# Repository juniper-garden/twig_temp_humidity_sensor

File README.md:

# twig_temp_humidity_sensor
Hardware files for the temperature and humidity sensor

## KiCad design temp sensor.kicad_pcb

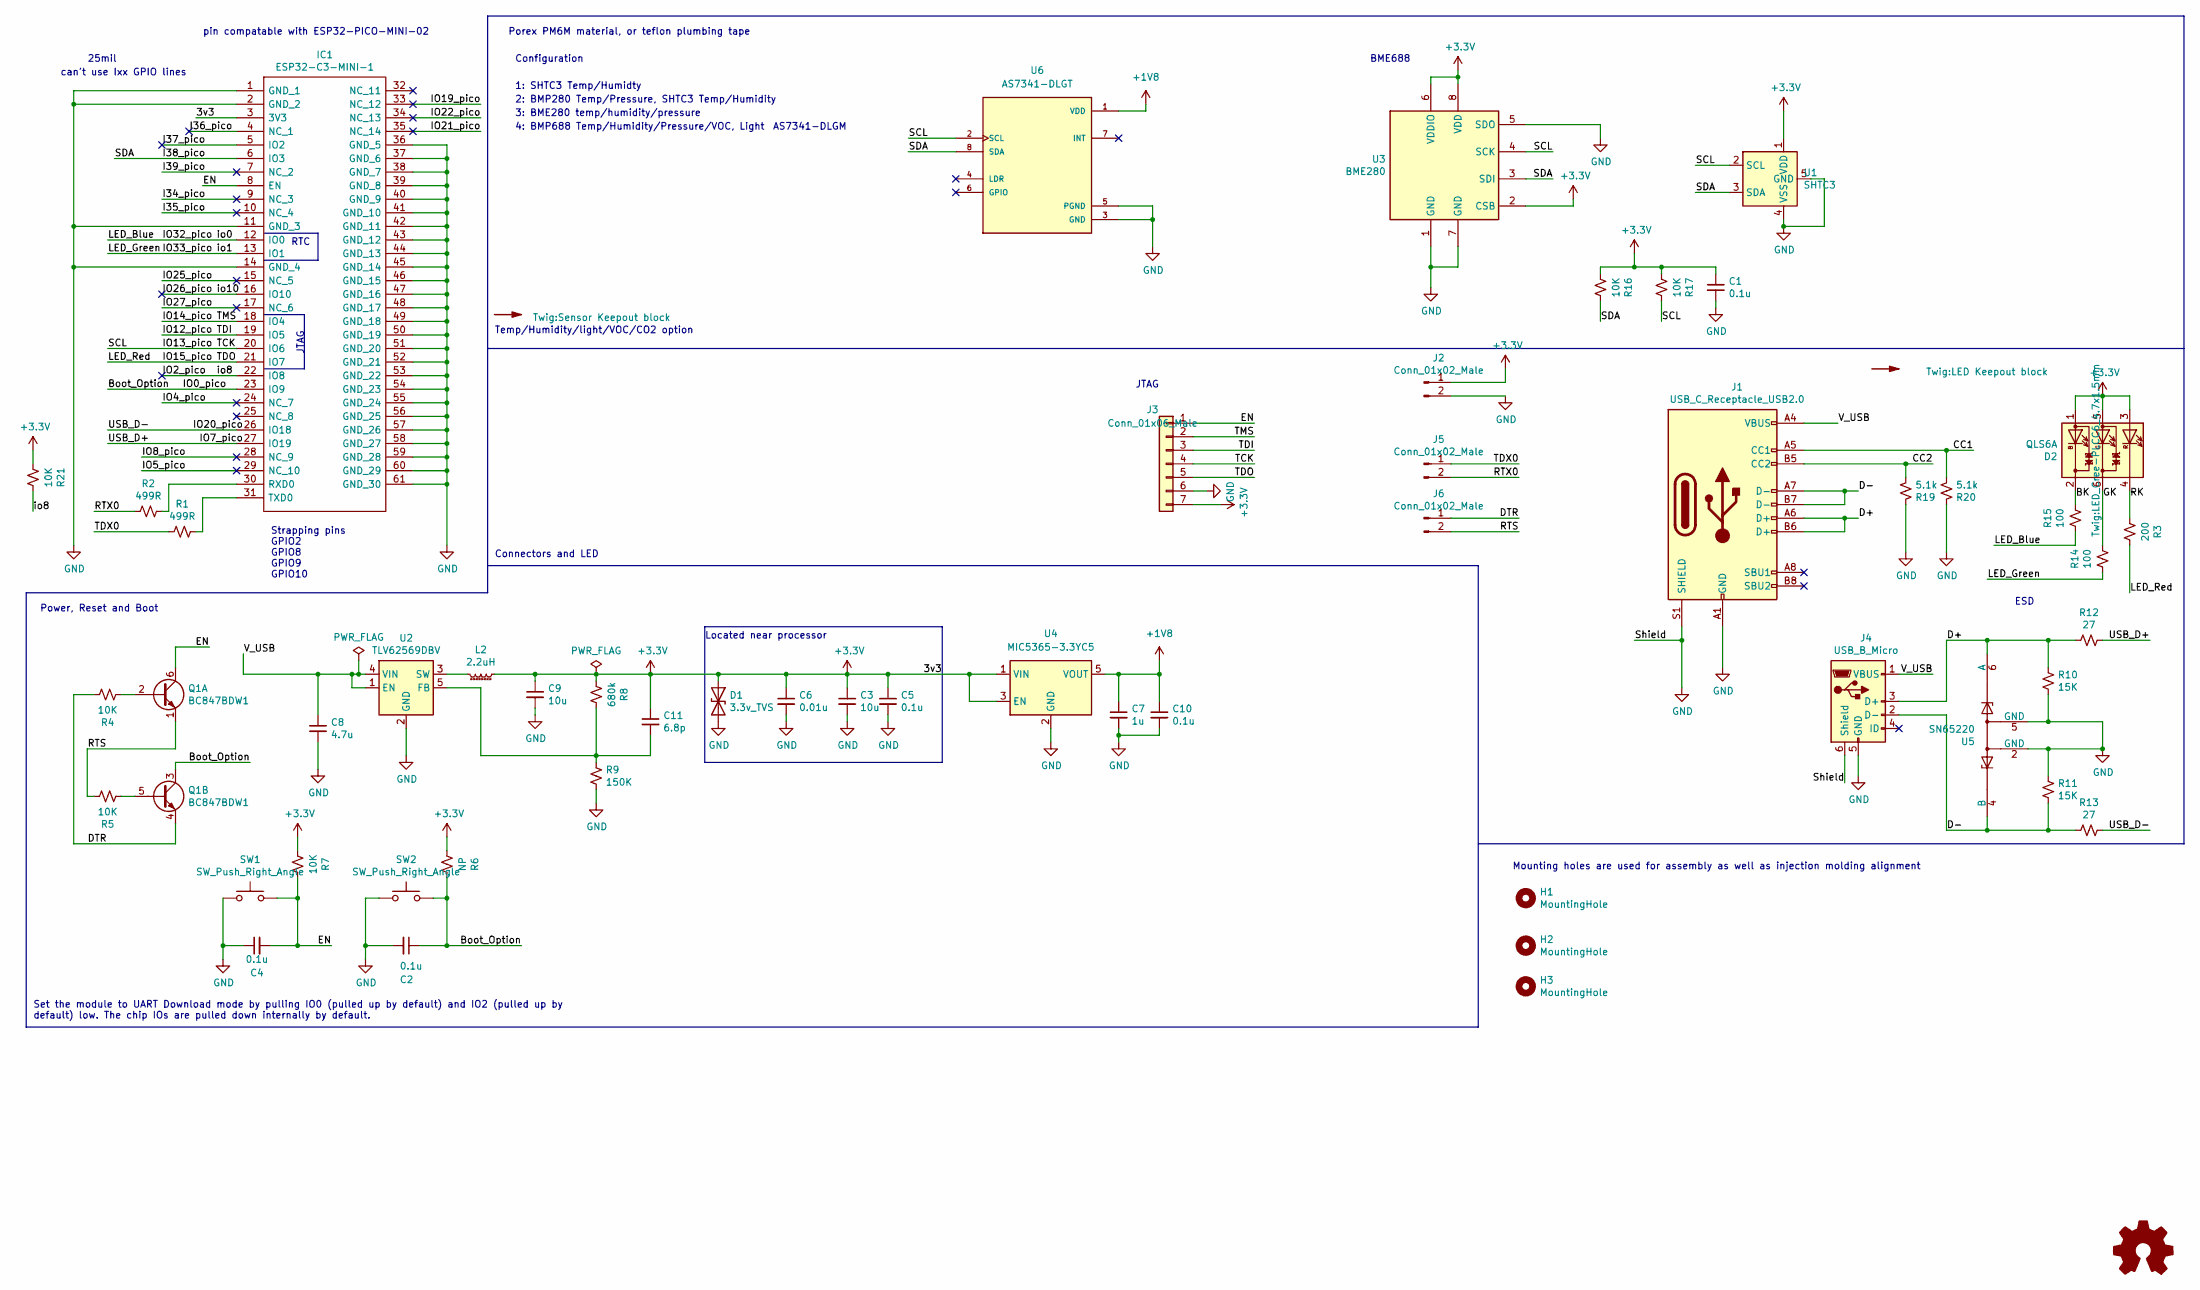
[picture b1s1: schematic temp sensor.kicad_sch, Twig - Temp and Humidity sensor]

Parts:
C1, C2, C4, C5, C10: 0.1u; C_0402_1005Metric; Manufacturer_Part_Number EMK105B7104KVHF; Mouser Part Number 963-EMK105B7104KVHF
C3, C9: 10u; C_1206_3216Metric_Pad1.42x1.75mm_HandSolder; Manufacturer_Part_Number LMK212ABJ106MG-T; Mouser Part Number 963-LMK212ABJ106MG-T
C6: 0.01u; C_0402_1005Metric; Manufacturer_Part_Number EMK105B7103KVHF; Mouser Part Number 963-EMK105B7103KVHF
C7: 1u; C_0603_1608Metric; Manufacturer_Part_Number EMK107B7105KA-T; Mouser Part Number 963-EMK107B7105KA-T
C8: 4.7u; C_0805_2012Metric; Manufacturer_Part_Number JMK107C6475KA-T; Mouser Part Number 963-JMK107C6475KA-T
C11: 6.8p; C_0402_1005Metric; Manufacturer_Part_Number EMK105B7103KVHF; Mouser Part Number 963-EMK105B7103KVHF
D1: 3.3v_TVS; D_SOD-323; Manufacturer_Part_Number SD03C-7; Mouser Part Number 621-SD03C-7
D2: QLS6A; LED_Cree-PLCC6_4.7x1.5mm; Manufacturer_Part_Number QLS6A-FKW-CNSNSF043; Mouser Part Number 941-QLS6AFKWNSNSF043
H1, H2, H3: MountingHole; CorePin_1.15mm; PARTREV V3
IC1: ESP32-C3-MINI-1; ESP32C3MINI1; Manufacturer_Part_Number ESP32-C3-MINI-1-H4; Mouser Part Number 356-ESP32-C3-MINI1H4
J1: USB_C_Receptacle_USB2.0; USB_C_Receptacle_HRO_TYPE-C-31-M-12; Manufacturer_Part_Number USB4105-GF-A; Mouser Part Number 640-USB4105-GF-A
J2, J5, J6: Conn_01x02_Male; PinHeader_1x02_P2.54mm_Vertical_SMD_Pin1Left
J3: Conn_01x06_Male; PinHeader_1x07_P1.00mm_Vertical_SMD_Pin1Right
J4: USB_B_Micro; USB_Micro-B_Molex-105017-0001; Manufacturer_Part_Number 105017-0001; Mouser Part Number 538-105017-0001
L2: 2.2uH; L_Taiyo-Yuden_MD-4040; Manufacturer_Part_Number MDMK4040T2R2MM; Mouser Part Number 963-MDMK4040T2R2MM
LOGO1: Logo_Open_Hardware_Small; FabDrawing-2Layer-Metric
Q1: BC847BDW1; SOT-363_SC-70-6; Manufacturer_Part_Number BC847BDW1T1G; Mouser Part Number 863-BC847BDW1T1G
R1, R2: 499R; R_0402_1005Metric; Manufacturer_Part_Number CR0603-FX-4990ELF; Mouser Part Number 652-CR0603FX-4990ELF
R3: 200; R_0402_1005Metric; Manufacturer_Part_Number CR0603-FX-2000ELF; Mouser Part Number 652-CR0603-FX2000ELF
R4, R5, R7, R16, R17, R21: 10K; R_0402_1005Metric; Manufacturer_Part_Number ESR03EZPJ103; Mouser Part Number 755-ESR03EZPJ103
R6: NP; R_0402_1005Metric; Manufacturer_Part_Number ESR03EZPJ103; Mouser Part Number 755-ESR03EZPJ103
R8: 680k; R_0402_1005Metric; Manufacturer_Part_Number RC0603FR-13680KL; Mouser Part Number 603-RC0603FR-13680KL
R9: 150K; R_0402_1005Metric; Manufacturer_Part_Number RC0603FR-07150KL; Mouser Part Number 603-RC0603FR-07150KL
R10, R11: 15K; R_0402_1005Metric; Manufacturer_Part_Number RC0603FR-1315KL; Mouser Part Number 603-RC0603FR-1315KL
R12, R13: 27; R_0402_1005Metric; Manufacturer_Part_Number RK73B1JTTDD270J; Mouser Part Number 660-RK73B1JTTDD270J
R14, R15: 100; R_0402_1005Metric; Manufacturer_Part_Number RC0603JR-07100RL; Mouser Part Number 603-RC0603JR-07100RL
R19, R20: 5.1k; R_0402_1005Metric; Manufacturer_Part_Number CR0603-FX-5101ELF; Mouser Part Number 652-CR0603FX-5101ELF
SW1, SW2: SW_Push_Right_Angle; SW_Push_1P1T-MP_NO_Horizontal_TL6340; Manufacturer_Part_Number TL6340AF160QG; Mouser Price/Stock $0.48/10000
SYM1: SYM_Arrow_Normal; Sensor Keepout block
SYM2: SYM_Arrow_Normal; LED Keepout block
U1: SHTC3; Sensirion_DFN-4-1EP_2x2mm_P1mm_EP0.7x1.6mm; Manufacturer_Part_Number SHTC3; Mouser Part Number 403-SHTC3
U2: TLV62569DBV; SOT-23-5; Manufacturer_Part_Number TLV62569DBVR; Mouser Part Number 595-TLV62569DBVR
U3: BME280; Bosch_LGA-8_2.5x2.5mm_P0.65mm_ClockwisePinNumbering; Manufacturer_Part_Number BME280; Mouser Part Number 262-BME280
U4: MIC5365-3.3YC5; SOT-353_SC-70-5
U5: SN65220; SOT-23-6; Manufacturer_Part_Number SN65220DBVT; Mouser Part Number 595-SN65220DBVT
U6: AS7341-DLGT; PSON80P310X200X110-8N; PARTREV V3

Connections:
+1V8: C7.1, C10.1, U4.5 (VOUT), U6.1 (VDD)
+3V3: C1.1, C3.1, C5.1, C6.1, C9.1, C11.1, D1.1 (A1), D2.1 (AB), D2.3 (AR), D2.5 (AG), IC1.3 (3V3), J2.1, J3.7, L2.2, R6.2, R7.2, R8.2, R16.2, R17.2, R21.2, U1.1 (VDD), U3.2 (CSB), U3.6 (VDDIO), U3.8 (VDD), U4.1 (VIN), U4.3 (EN)
/BK: D2.2 (KB), R15.1
/Boot_Option: C2.1, IC1.23 (IO9), Q1.3 (C2), R6.1, SW2.2
/CC1: J1.A5 (CC1), R20.2
/CC2: J1.B5 (CC2), R19.2
/D+: J1.A6 (D+), J1.B6 (D+), J4.3 (D+), R10.1, R12.1, U5.1, U5.6 (A)
/D-: J1.A7 (D-), J1.B7 (D-), J4.2 (D-), R11.2, R13.1, U5.3, U5.4 (B)
/DTR: J6.1, Q1.4 (E2), R4.1
/EN: C4.2, IC1.8 (EN), J3.1, Q1.6 (C1), R7.1, SW1.2
/GK: D2.6 (KR), R14.1
/I34_pico: IC1.9 (NC_3)
/I35_pico: IC1.10 (NC_4)
/I36_pico: IC1.4 (NC_1)
/I37_pico: IC1.5 (IO2)
/I38_pico: IC1.6 (IO3), R16.1, U1.3 (SDA), U3.3 (SDI), U6.8 (SDA)
/I39_pico: IC1.7 (NC_2)
/IO2_pico: IC1.22 (IO8), R21.1
/IO4_pico: IC1.24 (NC_7)
/IO5_pico: IC1.29 (NC_10)
/IO8_pico: IC1.28 (NC_9)
/IO12_pico: IC1.19 (IO5), J3.3
/IO13_pico: IC1.20 (IO6), J3.4, R17.1, U1.2 (SCL), U3.4 (SCK), U6.2 (SCL)
/IO14_pico: IC1.18 (IO4), J3.2
/IO15_pico: IC1.21 (IO7), J3.5, R3.1
/IO19_pico: IC1.33 (NC_12)
/IO21_pico: IC1.35 (NC_14)
/IO22_pico: IC1.34 (NC_13)
/IO25_pico: IC1.15 (NC_5)
/IO26_pico: IC1.16 (IO10)
/IO27_pico: IC1.17 (NC_6)
/IO32_pico: IC1.12 (IO0), R15.2
/IO33_pico: IC1.13 (IO1), R14.2
/RK: D2.4 (KR), R3.2
/RTS: J6.2, Q1.1 (E1), R5.1
/RTX0: J5.2, R2.2
/TDX0: J5.1, R1.2
/USB_D+: IC1.27 (IO19), R12.2
/USB_D-: IC1.26 (IO18), R13.2
/V_USB: C8.1, J1.A4 (VBUS), J1.A9 (VBUS), J1.B4 (VBUS), J1.B9 (VBUS), J4.1 (VBUS), U2.1 (EN), U2.4 (VIN)
GND: C1.2, C2.2, C3.2, C4.1, C5.2, C6.2, C7.2, C8.2, C9.2, C10.2, D1.2 (A2), IC1.1 (GND_1), IC1.2 (GND_2), IC1.11 (GND_3), IC1.14 (GND_4), IC1.36 (GND_5), IC1.37 (GND_6), IC1.38 (GND_7), IC1.39 (GND_8), IC1.40 (GND_9), IC1.41 (GND_10), IC1.42 (GND_11), IC1.43 (GND_12), IC1.44 (GND_13), IC1.45 (GND_14), IC1.46 (GND_15), IC1.47 (GND_16), IC1.48 (GND_17), IC1.49 (GND_18), IC1.50 (GND_19), IC1.51 (GND_20), IC1.52 (GND_21), IC1.53 (GND_22), IC1.54 (GND_23), IC1.55 (GND_24), IC1.56 (GND_25), IC1.57 (GND_26), IC1.58 (GND_27), IC1.59 (GND_28), IC1.60 (GND_29), IC1.61 (GND_30), J1.A1 (GND), J1.A12 (GND), J1.B1 (GND), J1.B12 (GND), J1.S1 (SHIELD), J2.2, J3.6, J4.5 (GND), J4.6 (Shield), R9.1, R10.2, R11.1, R19.1, R20.1, SW1.1, SW2.1, U1.4 (VSS), U1.5 (GND), U2.2 (GND), U3.1 (GND), U3.5 (SDO), U3.7 (GND), U4.2 (GND), U5.2 (GND), U5.5 (GND), U6.3 (GND), U6.5 (PGND)
unnamed: IC1.30 (RXD0), R2.1
unnamed: IC1.31 (TXD0), R1.1
unnamed: L2.1, U2.3 (SW)
unnamed: Q1.2 (B1), R4.2
unnamed: Q1.5 (B2), R5.2
unnamed: C11.2, R8.1, R9.2, U2.5 (FB)

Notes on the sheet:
4: BMP688 Temp/Humidity/Pressure/VOC, Light
AS7341-DLGM
BME688
ESD
JTAG
Set the module to UART Download mode by pulling IO0 (pulled up by default) and IO2 (pulled up by default) low. The chip IOs are pulled down internally by default.
pin compatable with ESP32-PICO-MINI-02
Power, Reset and Boot
Mounting holes are used for assembly as well as injection molding alignment
Configuration
Located near processor
1: SHTC3 Temp/Humidty
25mil
Strapping pins GPIO2 GPIO8 GPIO9 GPIO10
Connectors and LED
3: BME280 temp/humidity/pressure
RTC
2: BMP280 Temp/Pressure, SHTC3 Temp/Humidity
Temp/Humidity/light/VOC/CO2 option
Porex PM6M material, or teflon plumbing tape
can't use Ixx GPIO lines

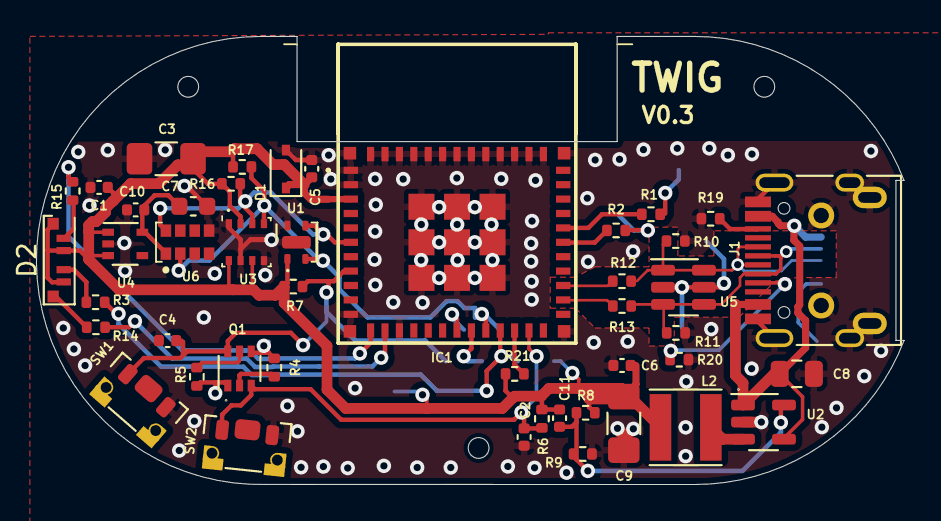
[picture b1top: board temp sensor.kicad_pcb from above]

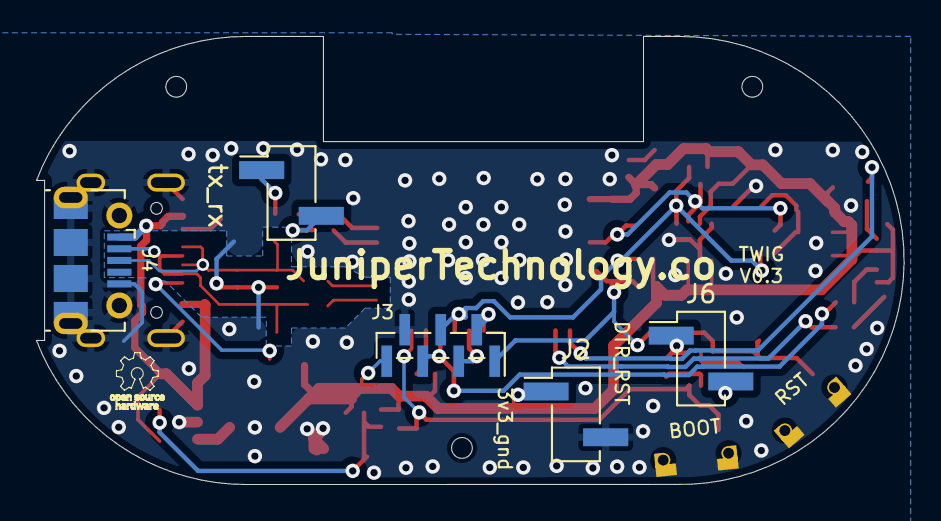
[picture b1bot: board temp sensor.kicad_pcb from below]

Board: 2 copper layers, 48.2 x 24.9 mm, 56 parts (5 on the bottom side), 33 nets.

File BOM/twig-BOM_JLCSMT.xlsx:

Comment | Designator | Footprint | JLCPCB Part #（optional）
0.1u | C1, C2, C4, C5 | Capacitor_SMD:C_0603_1608Metric | C14663
10u | C3, C9 | Capacitor_SMD:C_0805_2012Metric | C15850
0.01u | C6 | Capacitor_SMD:C_0603_1608Metric | C57112
4.7u | C8 | Capacitor_SMD:C_0805_2012Metric | C19702
3.3v_TVS | D1 | Diode_SMD:D_SOD-323_HandSoldering | C558442
QLS6A | D2 | LED_SMD:LED_Cree-PLCC6_4.7x1.5mm | N/A
6V 0.5A | F1 | Fuse:Fuse_0603_1608Metric | C207011
ESP32-C3-MINI-1 | IC1 | Twig:ESP32C3MINI1 | C2838502
USB_C_Receptacle_USB2.0 | J1 | Connector_USB:USB_C_Receptacle_HRO_TYPE-C-31-M-12 | C136423
L_Core_Ferrite_Small | L1 | Inductor_SMD:L_0603_1608Metric | C96995
2.2uH | L2 | Inductor_SMD:L_Taiyo-Yuden_MD-4040 | C142141
BC847BDW1 | Q1 | Package_TO_SOT_SMD:SOT-363_SC-70-6 | C426871
499R | R1, R2 | Resistor_SMD:R_0603_1608Metric | C23065
200r | R3 | Resistor_SMD:R_0603_1608Metric | C430229
10K | R4, R5, R6, R7, R16, R17 | Resistor_SMD:R_0603_1608Metric | C25804
680k | R8, R18 | Resistor_SMD:R_0603_1608Metric | C25822
150K | R9 | Resistor_SMD:R_0603_1608Metric | C22807
15K | R10, R11 | Resistor_SMD:R_0603_1608Metric | C22809
27r | R12, R13 | Resistor_SMD:R_0603_1608Metric | C25190
100r | R14, R15 | Resistor_SMD:R_0603_1608Metric | C22775
5.1k | R19, R20 | Resistor_SMD:R_0603_1608Metric | C23186
SW_Push_Right_Angle | SW1, SW2 | Twig:SW_Push_1P1T-MP_NO_Horizontal_TL6340 | C380198
SHTC3 | U1 | Sensor_Humidity:Sensirion_DFN-4-1EP_2x2mm_P1mm_EP0.7x1.6mm | C194656
TLV62569DBV | U2 | Package_TO_SOT_SMD:SOT-23-5 | C141836
BME280 | U3 | Package_LGA:Bosch_LGA-8_2.5x2.5mm_P0.65mm_ClockwisePinNumbering | C92489
Si7020-A20 | U4 | Package_DFN_QFN:DFN-6-1EP_3x3mm_P1mm_EP1.5x2.4mm | C430229
SN65220 | U5 | Package_TO_SOT_SMD:SOT-23-6 | C350555

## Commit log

2021-04-24 initial commit
    Added initial files to the repo
2021-05-01 added several parts, associated footprints, added todo list
2021-05-01 assigned designators Signed-off-by: lokimetasmith <lokimail@gmail.com>
2021-05-01 updated pdf
2021-05-04 minor update
2021-05-06 initial layout and silk screen options
2021-05-06 minor layout update and pic of humidity sensor cover concept
2021-05-08 layout and part changes
2021-05-11 bom and pcb changes, need to add a switch still.
2021-05-12 added alt parts Signed-off-by: lokimetasmith <lokimail@gmail.com>
2021-05-12 lots of layout changes, optimized RF pathway, adjusted pinout, still working on ESP32 pinout
2021-05-13 updated schematic for updated parts
2021-05-15 updated bom
2021-05-16 exported gerbers, initial board spin
2021-05-17 minor cosmetic updates
2021-06-15 first crack at v2
2021-06-17 switched resistors
2021-06-17 working on switch footprint
2021-06-20 added slot, updated led pins, updated buttons, still working on jtag and which IO to use
2021-06-22 updated footprints for switches, adjusted layout and cleaned up traces.
    Needs review but should be ready for second spin.
2021-07-06 added layout for usb C, lots of little changes to spacing. Still working out how much voltage protection is nessisary for usb-c
2021-07-08 added fuse and some layout changes
2021-07-12 Mostly all done, with Rev2. need to do final schematic review and logo
2021-07-13 reworked the layout to improve impedance, or so I hope.
2021-07-14 adding graphics and fab notes.
2021-07-14 updated bom, exported gerbers
2021-07-16 initial work on gerber files, there's an error where arches aren't rendered correctly
2021-07-20 gerbers as ordered for the panelized version 0.2 of the board
2021-08-30 updated drawings for readablity, exported pdf bom and manufacturing documentation
2021-09-21 updated models, added in zipped gerbers and 3D step files
2021-10-06 updated manufacturing notes
2021-10-07 updated design files
2021-10-07 slight change to documentation update, added dimensions of the board to help assist in fabrication
2021-10-13 added full outline and mold alignment holes
2021-10-14 updated silk to v0.2.1 for minor update to v0.2
2021-10-24 staging for 0.3, added footprint for everlight rgb-led (will shine into the board as opposed to out of board) moved esp32 closer to the edge to match edge graphic, no major circuit change from 0.2
2021-10-24 documentation updates
2021-10-24 added Thumbs.db to ignore list
2021-10-25 updated 0.3 bom and schematic
2021-10-29 version 0.4 includes JLCPCB changes and overmolding options
2022-01-03 Revert "Revert "Revert "version 0.4 includes JLCPCB changes and overmolding options"""
    This reverts commit 40e6c7e4762de2b8bfb4e926ce4de56b718958bf.
    Adds many features for jlcpcb
2022-01-03 updated ignore to ignore thumbs.db
2022-01-04 added step, flipped bme280 select to match adafruit bme280 breakout board
2022-02-21 updated to kicad 6, lots of changes
2022-02-21 exported v3 gerbers
2022-02-21 updated user.drawings with sensor window cutout
2022-02-22 added usb 3d step model
2022-03-10 added support for AS7341 and removed support for one of the temp/humidity sensors
2022-03-18 working to add the 3D overmold cutout to the step file
2022-03-21 added cutout model, minor changes to pcb
2022-03-24 added led cutout block
2022-04-11 cribbed schematic corrections from https://github.com/esp-rs/esp-rust-board/tree/master/hardware/esp-rust-board
    tweaked part layout, added back in zener 3v3 diode, added filter diode, and made minor tweaks.

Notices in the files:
temp sensor.kicad_sch:
Released under: https://creativecommons.org/licenses/by-sa/4.0
